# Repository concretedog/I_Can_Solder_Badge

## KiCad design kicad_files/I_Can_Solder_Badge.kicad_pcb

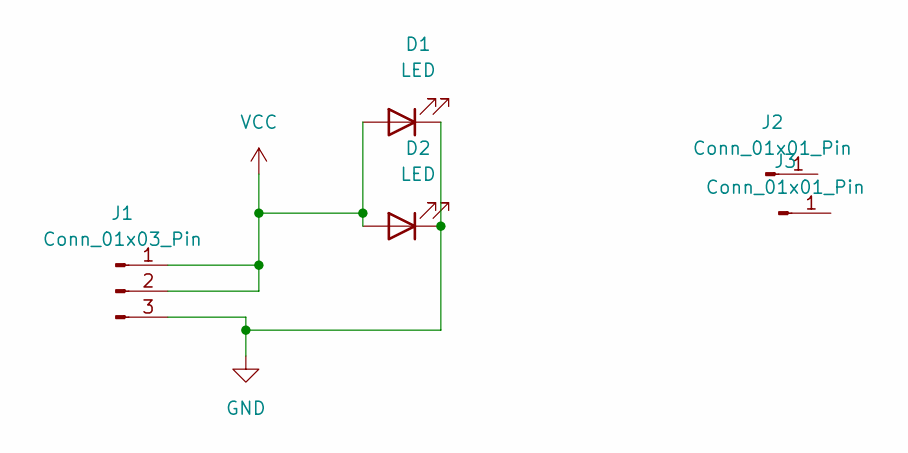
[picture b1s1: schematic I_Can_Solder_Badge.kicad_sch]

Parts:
D1, D2: LED; LED_D5.0mm
J1: Conn_01x03_Pin; CR2032_Battery_Holder_from_switch
J2, J3: Conn_01x01_Pin; PinHeader_1x01_P1.00mm_Vertical

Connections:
GND: D1.1 (K), D2.1 (K), J1.3
VCC: D1.2 (A), D2.2 (A), J1.1, J1.2

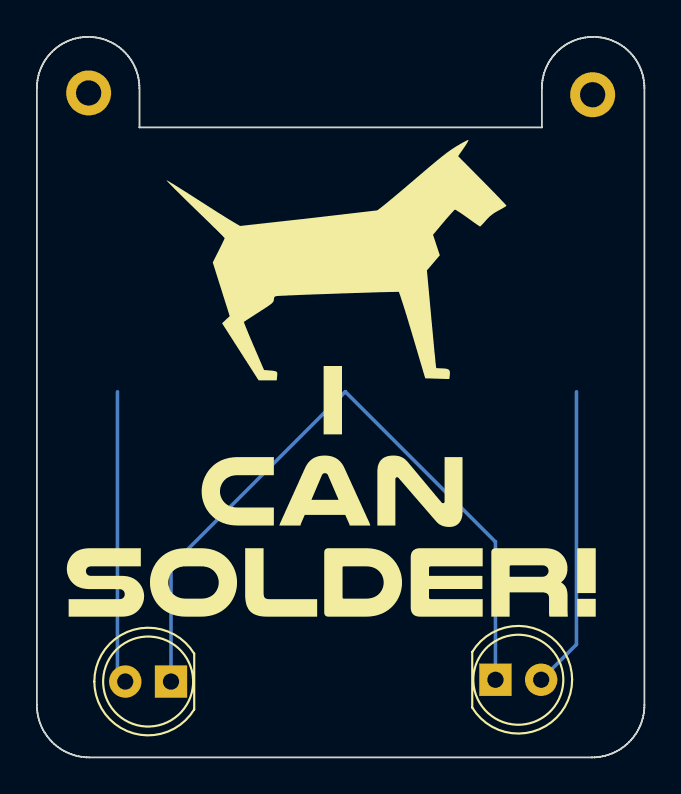
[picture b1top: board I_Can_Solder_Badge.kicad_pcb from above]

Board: 2 copper layers, 33.7 x 40.0 mm, 5 parts (0 on the bottom side), 2 nets.

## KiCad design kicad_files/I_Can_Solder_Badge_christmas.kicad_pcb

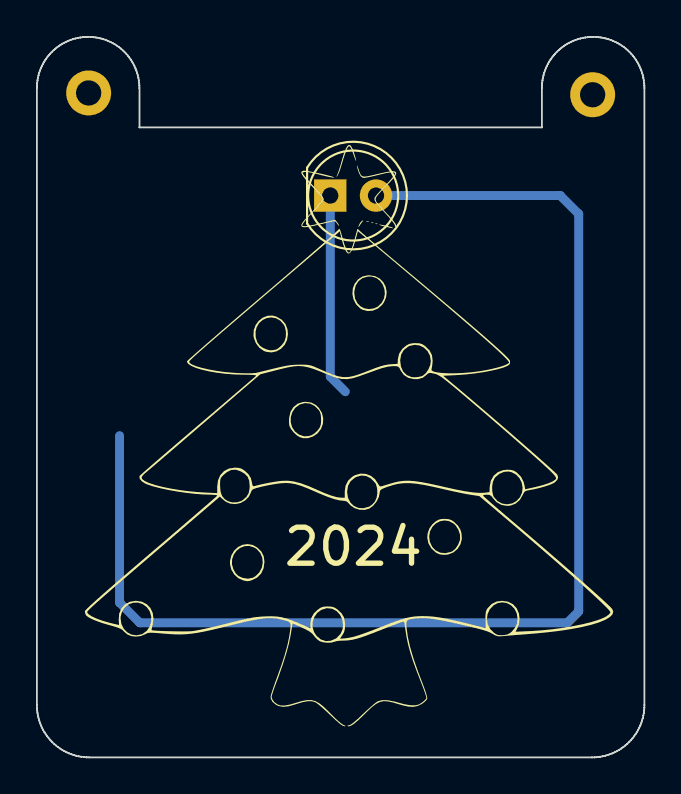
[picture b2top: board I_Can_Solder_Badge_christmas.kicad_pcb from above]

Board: 2 copper layers, 33.7 x 40.0 mm, 5 parts (0 on the bottom side), 2 nets.

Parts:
2024: LOGO
D2: LED; LED_D5.0mm
J1: Conn_01x03_Pin; CR2032_Battery_Holder_from_switch
J2, J3: Conn_01x01_Pin; PinHeader_1x01_P1.00mm_Vertical

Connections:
GND: D2.1 (K), J1.3
VCC: D2.2 (A), J1.1, J1.2

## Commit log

2024-11-28 Added Christmassy Badge
